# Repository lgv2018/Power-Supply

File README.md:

# Power-Supply
Power supply based on arduino
test on my laptop

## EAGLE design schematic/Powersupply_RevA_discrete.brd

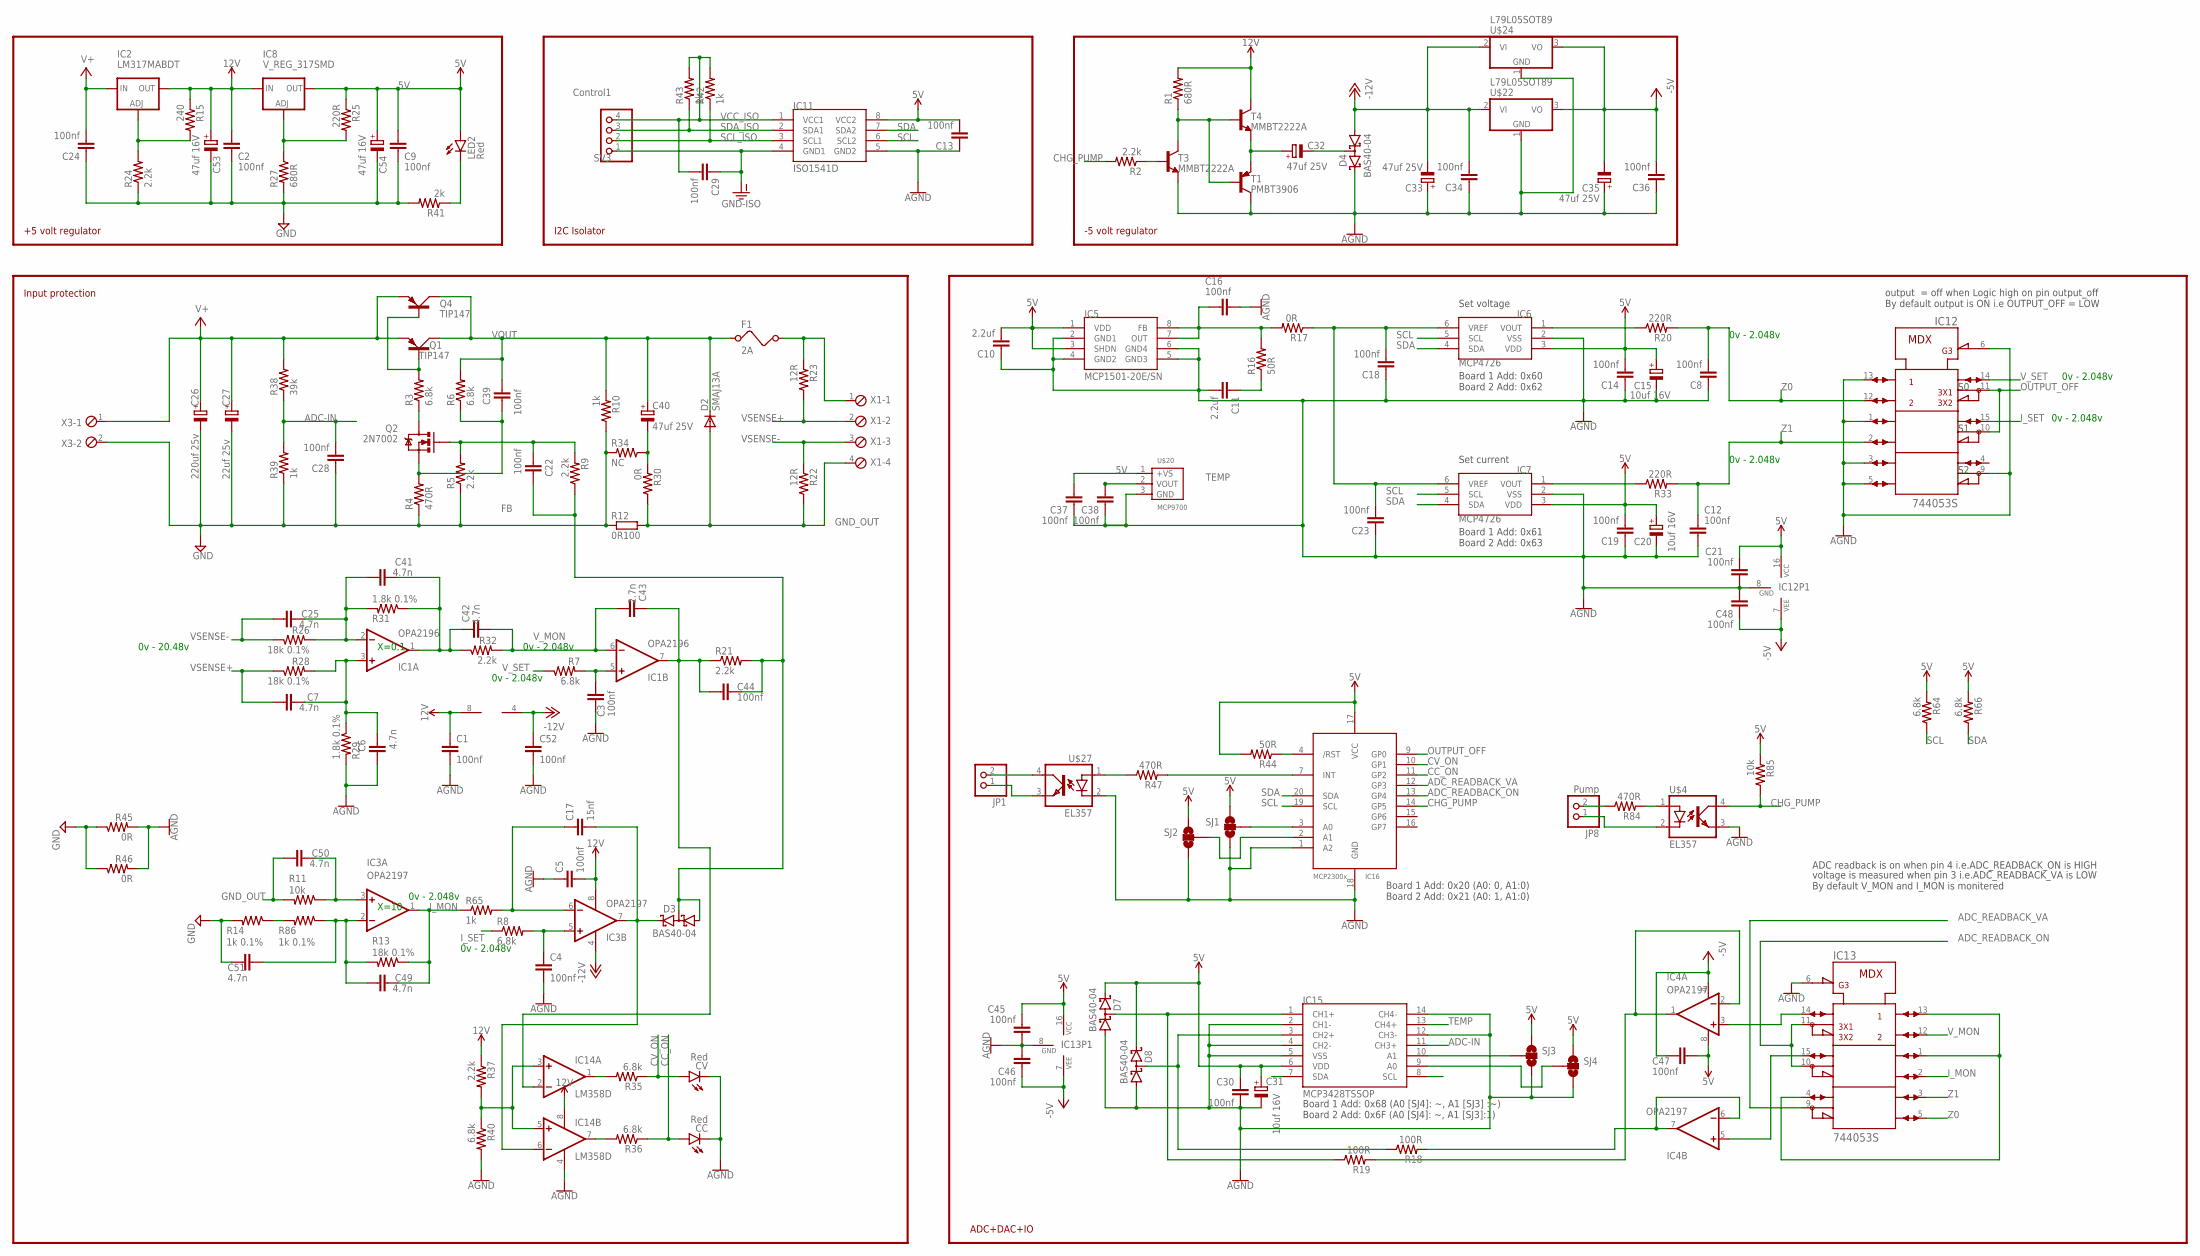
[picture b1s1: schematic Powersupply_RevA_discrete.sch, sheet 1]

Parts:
C1, C2, C3, C5, C8, C9, C12, C13, C14, C16, C18, C19, C21, C23, C24, C28, C29, C30, C34, C36, C37, C38, C39, C44, C45, C46, C47, C48, C52: 100nf; C0603
C4, C22: 100nf; C0805
C6, C7, C25, C41, C42, C49, C50, C51: 4.7n; C0805
C10, C11: 2.2uf; C0805
C15, C20, C31: 10uf 16V; E2-5
C17: 15nf; C0805
C26: 220uf 25v; E3,5-8
C27: 22uf 25v; E3,5-8
C32: 47uf 25V; CT6032
C33, C35, C40: 47uf 25V; E2-5
C43: 2.7n; C0805
C53, C54: 47uf 16V; E2-5
CC: Red; CHIP-LED0805
CV: Red; CHIP-LED0805
D2: SMAJ13A; DO214AC
D3, D4, D7, D8: BAS40-04; SOT23
F1: 2A; FUSE
IC1: OPA2196; SO08
IC2: LM317MABDT; DPACK
IC3, IC4: OPA2197; SO08
IC5: MCP1501-20E/SN; SO-08
IC6, IC7: MCP4726; SOT23-6
IC8: V_REG_317SMD; SOT223
IC11: ISO1541D; SO-08
IC12, IC13: 744053S; SO16
IC14: LM358D; SO08
IC15: MCP3428TSSOP; TSSOP14
IC16: MCP23008QFN20; QFN20
JP1: PINHD-1X2; 1X02
JP8: Pump; 1X02
LED2: Red; CHIP-LED0805
Q1: TIP147; TOP3AV
Q2: 2N7002; SOT23
Q4: TIP147; TO220AV
R1, R27: 680R; R0805
R2, R5, R9, R21, R24, R32, R37: 2.2k; R0805
R3, R6, R7, R8, R35, R36, R40, R64, R66: 6.8k; R0805
R4, R47, R84: 470R; R0805
R10, R39, R42, R43, R65: 1k; R0805
R11, R85: 10k; R0805
R12: 0R100; R2512
R13, R26, R28: 18k 0.1%; R0805
R14, R86: 1k 0.1%; R0805
R15: 240; R0805
R16, R44: 50R; R0805
R17, R30, R45, R46: 0R; R0805
R18, R19: 100R; R0805
R20, R25, R33: 220R; R0805
R22, R23: 12R; R0805
R29, R31: 1.8k 0.1%; R0603
R34: NC; R0805
R38: 39k; R0805
R41: 2k; R0805
SJ1, SJ2, SJ3, SJ4: SOLDERJUMPER_2WAY-OLDS; SJ_3
SV3: Control1; 1X04
T1: PMBT3906; SOT23-BEC
T3, T4: MMBT2222A; SOT23-BEC
U$4, U$27: EL357
U$20: MCP9700; TO92-BCE
U$22, U$24: L79L05SOT89; SOT89
X1: MPT4; 4POL254
X3: MPT2; 2POL254

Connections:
5V: C9.2, C10.2, C13.2, C14.2, C15.+, C19.2, C20.+, C21.2, C30.2, C31.+, C37.2, C45.2, C47.1, C54.+, D7.2 (C2), D8.2 (C2), IC4.8 (V+), IC5.1 (VDD), IC5.3 (SHDN), IC6.3 (VDD), IC7.3 (VDD), IC8.2 (OUT), IC11.8 (VCC2), IC12.16 (VCC), IC13.16 (VCC), IC15.6 (VDD), IC16.17 (VCC), LED2.A, R25.1, R44.2, R64.2, R66.2, R85.2, SJ1.1, SJ2.1, SJ3.1, SJ4.1, U$20.1 (+VS)
12V: C1.1, C2.2, C5.2, C53.+, IC1.8 (V+), IC2.4 (OUT), IC3.8 (V+), IC8.3 (IN), IC14.8 (V+), R1.2, R15.1, R37.1, T4.C
-5V: C35.-, C36.2, C46.1, C47.2, C48.1, IC4.4 (V-), IC12.7 (VEE), IC13.7 (VEE), U$22.3 (VO), U$24.3 (VO)
-12V: C33.-, C34.2, C52.1, D4.1 (A1), IC1.4 (V-), IC3.4 (V-), U$22.2 (VI), U$24.2 (VI)
ADC-IN: C28.2, IC15.11 (CH3+), R38.1, R39.2
ADC-IOUT: IC4.6 (-IN), IC4.7 (OUT), R18.2
ADC-VOUT: IC4.1 (OUT), IC4.2 (-IN), R19.2
ADC_READBACK_ON: IC13.10, IC13.11, IC16.13 (GP4)
ADC_READBACK_VA: IC13.9, IC16.12 (GP3)
AGND: C1.2, C3.2, C4.2, C5.1, C6.2, C8.1, C10.1, C11.2, C12.1, C13.1, C14.1, C15.-, C16.2, C18.1, C19.1, C20.-, C21.1, C23.1, C30.1, C31.-, C33.+, C34.1, C35.+, C36.1, C37.1, C38.1, C45.1, C46.2, C48.2, C52.2, CC.C, CV.C, D4.2 (C2), D7.1 (A1), D8.1 (A1), IC5.2 (GND1), IC5.4 (GND2), IC5.5 (GND3), IC5.6 (GND4), IC6.2 (VSS), IC7.2 (VSS), IC11.5 (GND2), IC12.1, IC12.3, IC12.5, IC12.6 (!G), IC12.8 (GND), IC12.9, IC12.13, IC13.6 (!G), IC13.8 (GND), IC14.4 (V-), IC15.2 (CH1-), IC15.4 (CH2-), IC15.5 (VSS), IC15.12 (CH3-), IC15.14 (CH4-), IC16.1 (A2), IC16.18 (GND), R29.2, R40.2, R45.2, R46.2, SJ1.3, SJ2.3, SJ3.3, SJ4.3, T1.C, T3.E, U$4.3 (EMIT), U$20.3 (GND), U$22.1 (GND), U$24.1 (GND), U$27.2 (C)
CC_ON: CC.A, IC16.11 (GP2), R36.1
CHG_PUMP: IC16.14 (GP5), R2.2, R85.1, U$4.4 (COL)
CV_ON: CV.A, IC16.10 (GP1), R35.1
FB: C22.2, C44.1, D3.1 (A1), D3.3 (C1A2), R9.1, R21.2
GND: C2.1, C9.1, C24.1, C26.-, C27.-, C28.1, C51.1, C53.-, C54.-, R4.1, R5.1, R10.1, R12.1, R14.2, R24.1, R27.2, R34.2, R39.1, R41.2, R45.1, R46.1, X3.2; also elsewhere on the board
GND-ISO: C29.1, IC11.4 (GND1), SV3.1
GND_OUT: C50.2, D2.A, R11.2, R12.2, R22.1, R30.1, X1.4
I_MON: C49.1, IC3.1 (OUT), IC13.2, R13.1, R65.1
I_SET: IC12.15, R8.1
unnamed: C17.1, IC3.6 (-IN), R65.2
unnamed: IC2.1 (ADJ), R15.2, R24.2
unnamed: C50.1, IC3.3 (+IN), R11.1
unnamed: C49.2, C51.2, IC3.2 (-IN), R13.2, R86.1
unnamed: F1.2, R23.2, X1.1
unnamed: R47.1, U$27.1 (A)
unnamed: C25.1, C41.2, IC1.2 (-IN), R26.2, R31.2
unnamed: C16.1, IC5.7 (OUT), IC5.8 (FB), R16.2, R17.2
unnamed: IC14.3 (+IN), IC14.5 (+IN), R37.2, R40.1
unnamed: C43.2, C44.2, IC1.7 (OUT), IC14.2 (-IN), R21.1
unnamed: C6.1, C7.1, IC1.3 (+IN), R28.2, R29.1
unnamed: C17.2, D3.2 (C2), IC3.7 (OUT), IC14.6 (-IN)
unnamed: IC8.1 (ADJ), R25.2, R27.1
unnamed: IC7.1 (VOUT), R33.1
unnamed: C11.1, R16.1
unnamed: C3.1, IC1.5 (+IN), R7.2
unnamed: C4.1, IC3.5 (+IN), R8.2
unnamed: D8.3 (C1A2), IC15.3 (CH2+), R18.1
unnamed: C40.-, R30.2, R34.1
unnamed: IC16.4 (/RST), R44.1
unnamed: IC16.3 (A0), SJ1.2
unnamed: IC4.3 (+IN), IC13.14
unnamed: Q1.B, Q4.B, R3.2
unnamed: LED2.C, R41.1
unnamed: IC4.5 (+IN), IC13.15
unnamed: D7.3 (C1A2), IC15.1 (CH1+), R19.1
unnamed: IC14.1 (OUT), R35.2
unnamed: IC16.2 (A1), SJ2.2
unnamed: IC15.10 (A1), SJ3.2
unnamed: IC15.9 (A0), SJ4.2
unnamed: R2.1, T3.B
unnamed: Q2.3 (D), R3.1
unnamed: R1.1, T1.B, T3.C, T4.B
unnamed: IC13.1, IC13.4, IC13.13
unnamed: C32.+, T1.E, T4.E
unnamed: C32.-, D4.3 (C1A2)
unnamed: IC6.1 (VOUT), R20.1
unnamed: C22.1, Q2.1 (G), R5.2, R9.2
unnamed: IC14.7 (OUT), R36.2
unnamed: C39.1, Q2.2 (S), R4.2, R6.1
unnamed: JP1.2, U$27.4 (COL)
unnamed: C41.1, C42.2, IC1.1 (OUT), R31.1, R32.1
unnamed: JP1.1, U$27.3 (EMIT)
unnamed: IC16.7 (INT), R47.2
unnamed: JP8.2, R84.1
unnamed: R84.2, U$4.1 (A)
unnamed: JP8.1, U$4.2 (C)
unnamed: R14.1, R86.2
OUTPUT_OFF: IC12.10, IC12.11, IC16.9 (GP0)
SCL: IC6.5 (SCL), IC7.5 (SCL), IC11.6 (SCL2), IC15.8 (SCL), IC16.19 (SCL), R64.1
SCL_ISO: IC11.3 (SCL1), R42.1, SV3.2
SDA: IC6.4 (SDA), IC7.4 (SDA), IC11.7 (SDA2), IC15.7 (SDA), IC16.20 (SDA), R66.1
SDA_ISO: IC11.2 (SDA1), R43.1, SV3.3
TEMP: C38.2, IC15.13 (CH4+), U$20.2 (VOUT)
V+: C24.2, C26.+, C27.+, IC2.3 (IN), Q1.E, Q4.E, R38.2, X3.1
VCC_ISO: C29.2, IC11.1 (VCC1), R42.2, R43.2, SV3.4
VOUT: C39.2, C40.+, D2.C, F1.1, Q1.C, Q4.C, R6.2, R10.2
VREF: C18.2, C23.2, IC6.6 (VREF), IC7.6 (VREF), R17.1
VSENSE+: C7.2, R23.1, R28.1, X1.2
VSENSE-: C25.2, R22.2, R26.1, X1.3
V_MON: C42.1, C43.1, IC1.6 (-IN), IC13.12, R32.2
V_SET: IC12.14, R7.1
Z0: C8.2, IC12.12, IC13.5, R20.2
Z1: C12.2, IC12.2, IC13.3, R33.2

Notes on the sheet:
+5 volt regulator
ADC+DAC+IO
Input protection
Board 1 Add: 0x60 Board 2 Add: 0x62
Board 1 Add: 0x61 Board 2 Add: 0x63
Board 1 Add: 0x68 (A0 [SJ4]: ~, A1 [SJ3] :~) Board 2 Add: 0x6F (A0 [SJ4]: ~, A1 [SJ3]:1)
Set voltage
Set current
X=10
X=0.1
0v - 20.48v
0v - 2.048v
-5 volt regulator
I2C Isolator
output = off when Logic high on pin output_off By default output is ON i.e OUTPUT_OFF = LOW
ADC readback is on when pin 4 i.e.ADC_READBACK_ON is HIGH
voltage is measured when pin 3 i.e.ADC_READBACK_VA is LOW By default V_MON and I_MON is monitered
Board 1 Add: 0x20 (A0: 0, A1:0) Board 2 Add: 0x21 (A0: 1, A1:0)

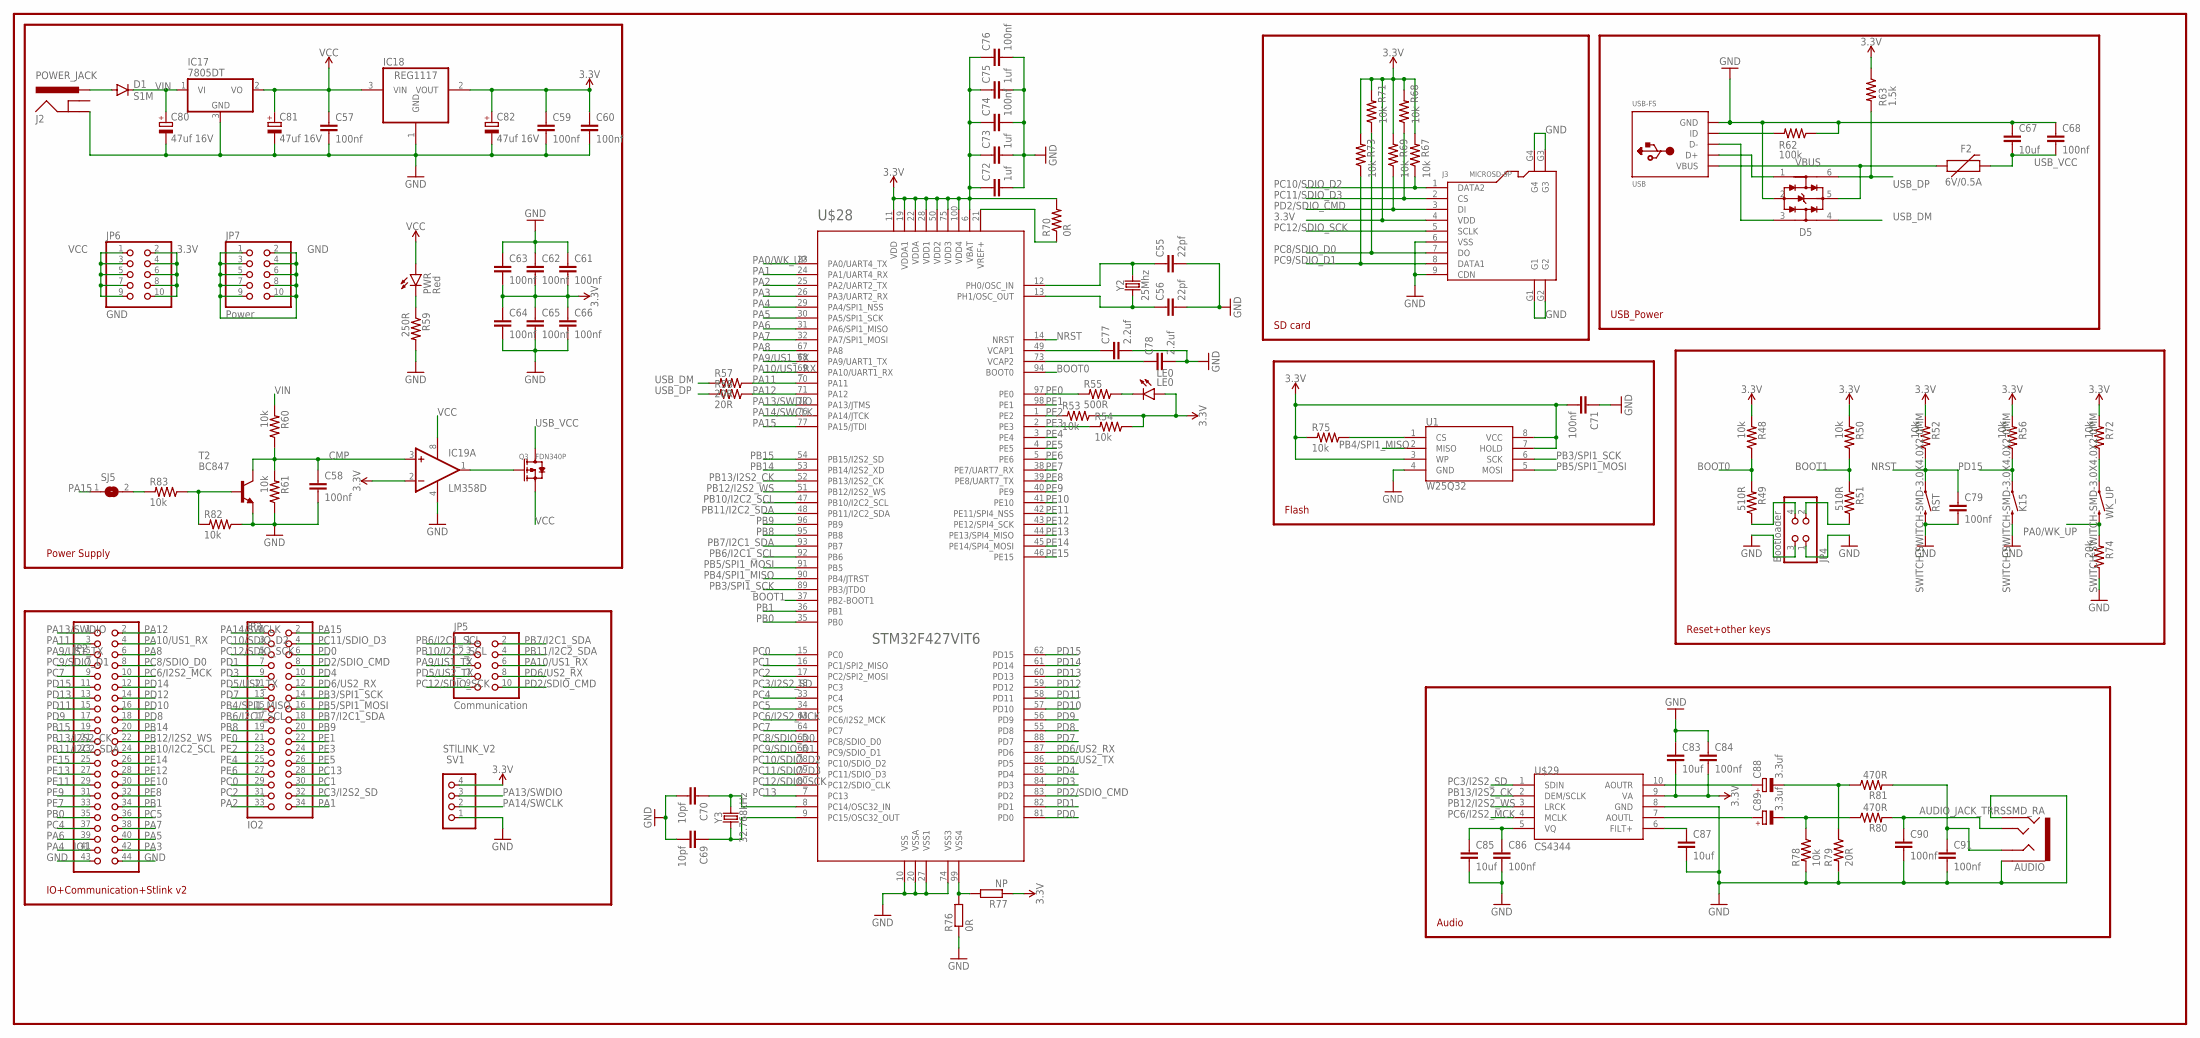
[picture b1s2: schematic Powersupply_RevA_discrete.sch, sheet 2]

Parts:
AUDIO: AUDIO_JACK_TRRSSMD_RA; AUDIO_JACK_3.5MM_TRRS_SMD_RA
C55, C56: 22pf; C0805
C57, C58, C59, C60, C61, C62, C63, C64, C65, C66, C68, C71, C74, C76, C79, C84, C86, C90, C91: 100nf; C0603
C67: 10uf; C0805
C69, C70: 10pf; C0805
C72, C73, C75: 1uf; C0805
C77, C78: 2.2uf; C0805
C80, C81, C82: 47uf 16V; E2-5
C83, C85, C87: 10uf; C1210
C88, C89: 3.3uf; A/3216-18R
D1: S1M; SMA
D5: USBLC6-2P; SOT23-6
F2: 6V/0.5A; 1206
IC17: 7805DT; TO252
IC18: REG1117; SOT223
IC19: LM358D; SO08
J2: POWER_JACK; POWER_JACK_PTH
J3: MICROSD-9P; MICRO-SD9+4P-SMD-16.1X14.5X1.85MM
JP2: IO1; 2X22
JP3: IO2; 2X17
JP4: Bootloader; 2X02
JP5: Communication; 2X05
JP6: GND; 2X05
JP7: Power; 2X05
K15: SWITCH-SWITCH-SMD-3.0X4.0X2.0MM; TACTILE_SWITCH_SMD_6.0X3.5MM
LE0: LE0; CHIP-LED0805
PWR: Red; CHIP-LED0805
Q3: FDN340P; SOT-23
R48, R50, R52, R53, R54, R56, R60, R61, R67, R68, R69, R71, R72, R73, R75, R78, R82, R83: 10k; R0805
R49, R51: 510R; R0805
R55: 500R; R0805
R57, R58, R79: 20R; R0805
R59: 250R; R0805
R62: 100k; R0805
R63: 1.5k; R0805
R70: 0R; R0805
R74: 20k; R0805
R76: 0R; R0402
R77: NP; R0402
R80, R81: 470R; R0805
RST: SWITCH-SWITCH-SMD-3.0X4.0X2.0MM; TACTILE_SWITCH_SMD_6.0X3.5MM
SJ5: SJ
SV1: STlLINK_V2; 1X04
T2: BC847; SOT23
U1: W25Q32; SO08
U$28: STM32F427VIT6; LQFP100
U$29: CS4344; TSSOP10
USB: USB-FS; USB-MINIB
WK_UP: SWITCH-SWITCH-SMD-3.0X4.0X2.0MM; TACTILE_SWITCH_SMD_6.0X3.5MM
Y2: 25Mhz; CRYSTAL-SMD-3.2X2.5MM
Y3: 32.768kHz; CRYSTAL-PTH-2X6-CYL

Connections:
3.3V: C59.1, C60.1, C61.2, C62.2, C63.2, C64.1, C65.1, C66.1, C71.2, C72.1, C73.1, C74.1, C75.1, C76.1, C82.+, C83.2, C84.2, IC18.2 (VOUT), IC19.2 (-IN), J3.4 (VDD), JP6.2, JP6.4, JP6.6, JP6.8, JP6.10, LE0.A, R48.2, R50.2, R52.2, R53.1, R54.1, R56.2, R63.1, R67.2, R68.2, R69.2, R70.2, R71.2, R72.2, R73.2, R75.2, R77.1, SV1.4, U1.3 (WP), U1.7 (HOLD), U1.8 (VCC), U$28.6 (VBAT), U$28.11 (VDD), U$28.19 (VDDA1), U$28.22 (VDDA), U$28.28 (VDD1), U$28.50 (VDD2), U$28.75 (VDD3), U$28.100 (VDD4), U$29.9 (VA)
BOOT0: R48.1, R49.2, U$28.94 (BOOT0)
BOOT1: R50.1, R51.2, U$28.37 (PB2-BOOT1)
CMP: C58.1, IC19.3 (+IN), R60.1, R61.2, T2.3 (C)
GND: AUDIO.EARTH, AUDIO.RING2, C55.2, C56.2, C57.2, C58.2, C59.2, C60.2, C61.1, C62.1, C63.1, C64.2, C65.2, C66.2, C67.1, C68.1, C69.2, C70.2, C71.1, C72.2, C73.2, C74.2, C75.2, C76.2, C77.2, C78.2, C79.2, C80.-, C81.-, C82.-, C83.1, C84.1, C85.2, C86.2, C87.2, C90.2, C91.2, D5.2 (GND), IC17.3 (GND), IC18.1 (GND), IC19.4 (V-), J2.GND, J3.6 (VSS), J3.9 (CDN), J3.G1, J3.G2, J3.G3, J3.G4, JP2.43, JP2.44, JP4.1, JP4.3, JP7.1, JP7.2, JP7.3, JP7.4, JP7.5, JP7.6, JP7.7, JP7.8, JP7.9, JP7.10, K15.2, R59.2, R61.1, R62.1, R74.1, R76.1, R78.2, R79.2, R82.1, RST.2, SV1.1, T2.2 (E), U1.4 (GND), U$28.10 (VSS), U$28.20 (VSSA), U$28.27 (VSS1), U$28.74 (VSS3), U$29.8 (GND), USB.GND; also elsewhere on the board
unnamed: C55.1, U$28.12 (PH0/OSC_IN), Y2.3 (2)
unnamed: C56.1, U$28.13 (PH1/OSC_OUT), Y2.1
unnamed: IC19.1 (OUT), Q3.1 (G)
unnamed: C69.1, U$28.9 (PC15/OSC32_OUT), Y3.1
unnamed: C70.1, U$28.8 (PC14/OSC32_IN), Y3.2
unnamed: R62.2, USB.ID
unnamed: LE0.C, R55.1
unnamed: D1.A, J2.PWR
unnamed: C77.1, U$28.49 (VCAP1)
unnamed: C78.1, U$28.73 (VCAP2)
unnamed: PWR.C, R59.1
unnamed: D5.1 (I/O1-IN), USB.D+
unnamed: JP4.4, R49.1
unnamed: JP4.2, R51.1
unnamed: R82.2, R83.1, T2.1 (B)
unnamed: R83.2, SJ5.2
unnamed: R70.1, U$28.21 (VREF+)
unnamed: R72.1, WK_UP.1
unnamed: R75.1, U1.1 (CS)
unnamed: D5.3 (I/O2-IN), USB.D-
unnamed: R76.2, R77.2, U$28.99 (VSS4)
unnamed: C87.1, U$29.6 (FILT+)
unnamed: C85.1, C86.1, U$29.5 (VQ)
unnamed: C88.+, U$29.10 (AOUTR)
unnamed: C89.+, U$29.7 (AOUTL)
unnamed: C89.-, R78.1, R80.1
unnamed: C88.-, R79.1, R81.1
unnamed: AUDIO.TIP, C90.1, R80.2
unnamed: AUDIO.RING1, C91.1, R81.2
NRST: C79.1, R52.1, RST.1, U$28.14 (NRST)
PA0/WK_UP: R74.2, U$28.23 (PA0/UART4_TX), WK_UP.2
PA1: JP3.34, U$28.24 (PA1/UART4_RX)
PA2: JP3.33, U$28.25 (PA2/UART2_TX)
PA3: JP2.42, U$28.26 (PA3/UART2_RX)
PA4: JP2.41, U$28.29 (PA4/SPI1_NSS)
PA5: JP2.40, U$28.30 (PA5/SPI1_SCK)
PA6: JP2.39, U$28.31 (PA6/SPI1_MISO)
PA7: JP2.38, U$28.32 (PA7/SPI1_MOSI)
PA8: JP2.6, U$28.67 (PA8)
PA9/US1_TX: JP2.5, JP5.5, U$28.68 (PA9/UART1_TX)
PA10/US1_RX: JP2.4, JP5.6, U$28.69 (PA10/UART1_RX)
PA11: JP2.3, R57.1, U$28.70 (PA11)
PA12: JP2.2, R58.1, U$28.71 (PA12)
PA13/SWDIO: JP2.1, SV1.3, U$28.72 (PA13/JTMS)
PA14/SWCLK: JP3.1, SV1.2, U$28.76 (PA14/JTCK)
PA15: JP3.2, SJ5.1, U$28.77 (PA15/JTDI)
PB0: JP2.35, U$28.35 (PB0)
PB1: JP2.34, U$28.36 (PB1)
PB3/SPI1_SCK: JP3.14, U1.6 (SCK), U$28.89 (PB3/JTDO)
PB4/SPI1_MISO: JP3.15, U1.2 (MISO), U$28.90 (PB4/JTRST)
PB5/SPI1_MOSI: JP3.16, U1.5 (MOSI), U$28.91 (PB5)
PB6/I2C1_SCL: JP3.17, JP5.1, U$28.92 (PB6)
PB7/I2C1_SDA: JP3.18, JP5.2, U$28.93 (PB7)
PB8: JP3.19, U$28.95 (PB8)
PB9: JP3.20, U$28.96 (PB9)
PB10/I2C2_SCL: JP2.24, JP5.3, U$28.47 (PB10/I2C2_SCL)
PB11/I2C2_SDA: JP2.23, JP5.4, U$28.48 (PB11/I2C2_SDA)
PB12/I2S2_WS: JP2.22, U$28.51 (PB12/I2S2_WS), U$29.3 (LRCK)
PB13/I2S2_CK: JP2.21, U$28.52 (PB13/I2S2_CK), U$29.2 (DEM/SCLK)
PB14: JP2.20, U$28.53 (PB14/I2S2_XD)
PB15: JP2.19, U$28.54 (PB15/I2S2_SD)
PC0: JP3.29, U$28.15 (PC0)
PC1: JP3.30, U$28.16 (PC1/SPI2_MISO)
PC2: JP3.31, U$28.17 (PC2/SPI2_MOSI)
PC3/I2S2_SD: JP3.32, U$28.18 (PC3), U$29.1 (SDIN)
PC4: JP2.37, U$28.33 (PC4)
PC5: JP2.36, U$28.34 (PC5)
PC6/I2S2_MCK: JP2.10, U$28.63 (PC6/I2S2_MCK), U$29.4 (MCLK)
PC7: JP2.9, U$28.64 (PC7)
PC8/SDIO_D0: J3.7 (DO), JP2.8, R71.1, U$28.65 (PC8/SDIO_D0)
PC9/SDIO_D1: J3.8 (DATA1), JP2.7, R73.1, U$28.66 (PC9/SDIO_D1)
PC10/SDIO_D2: J3.1 (DATA2), JP3.3, R67.1, U$28.78 (PC10/SDIO_D2)
PC11/SDIO_D3: J3.2 (CS), JP3.4, R68.1, U$28.79 (PC11/SDIO_D3)
PC12/SDIO_SCK: J3.5 (SCLK), JP3.5, JP5.9, U$28.80 (PC12/SDIO_CLK)
PC13: JP3.28, U$28.7 (PC13)
PD0: JP3.6, U$28.81 (PD0)
PD1: JP3.7, U$28.82 (PD1)
PD2/SDIO_CMD: J3.3 (DI), JP3.8, JP5.10, R69.1, U$28.83 (PD2)
PD3: JP3.9, U$28.84 (PD3)
PD4: JP3.10, U$28.85 (PD4)
PD5/US2_TX: JP3.11, JP5.7, U$28.86 (PD5)
PD6/US2_RX: JP3.12, JP5.8, U$28.87 (PD6)
PD7: JP3.13, U$28.88 (PD7)
PD8: JP2.18, U$28.55 (PD8)
PD9: JP2.17, U$28.56 (PD9)
PD10: JP2.16, U$28.57 (PD10)
PD11: JP2.15, U$28.58 (PD11)
PD12: JP2.14, U$28.59 (PD12)
PD13: JP2.13, U$28.60 (PD13)
PD14: JP2.12, U$28.61 (PD14)
PD15: JP2.11, K15.1, R56.1, U$28.62 (PD15)
PE0: JP3.21, R55.2, U$28.97 (PE0)
PE1: JP3.22, U$28.98 (PE1)
PE2: JP3.23, R53.2, U$28.1 (PE2)
PE3: JP3.24, R54.2, U$28.2 (PE3)
PE4: JP3.25, U$28.3 (PE4)
PE5: JP3.26, U$28.4 (PE5)
PE6: JP3.27, U$28.5 (PE6)
PE7: JP2.33, U$28.38 (PE7/UART7_RX)
PE8: JP2.32, U$28.39 (PE8/UART7_TX)
PE9: JP2.31, U$28.40 (PE9)
PE10: JP2.30, U$28.41 (PE10)
PE11: JP2.29, U$28.42 (PE11/SPI4_NSS)
PE12: JP2.28, U$28.43 (PE12/SPI4_SCK)
PE13: JP2.27, U$28.44 (PE13/SPI4_MISO)
PE14: JP2.26, U$28.45 (PE14/SPI4_MOSI)
PE15: JP2.25, U$28.46 (PE15)
USB_DM: D5.4 (I/O2-OUT), R57.2
USB_DP: D5.6 (I/O1-OUT), R58.2, R63.2
USB_VCC: C67.2, C68.2, F2.2, Q3.3 (D)
VBUS: D5.5 (VBUS), F2.1, USB.VBUS
VCC: C57.1, C81.+, IC17.2 (VO), IC18.3 (VIN), IC19.8 (V+), JP6.1, JP6.3, JP6.5, JP6.7, JP6.9, PWR.A, Q3.2 (S)
VIN: C80.+, D1.C, IC17.1 (VI), R60.2

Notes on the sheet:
Power Supply
IO+Communication+Stlink v2
SD card
Flash
USB_Power
Reset+other keys
Audio

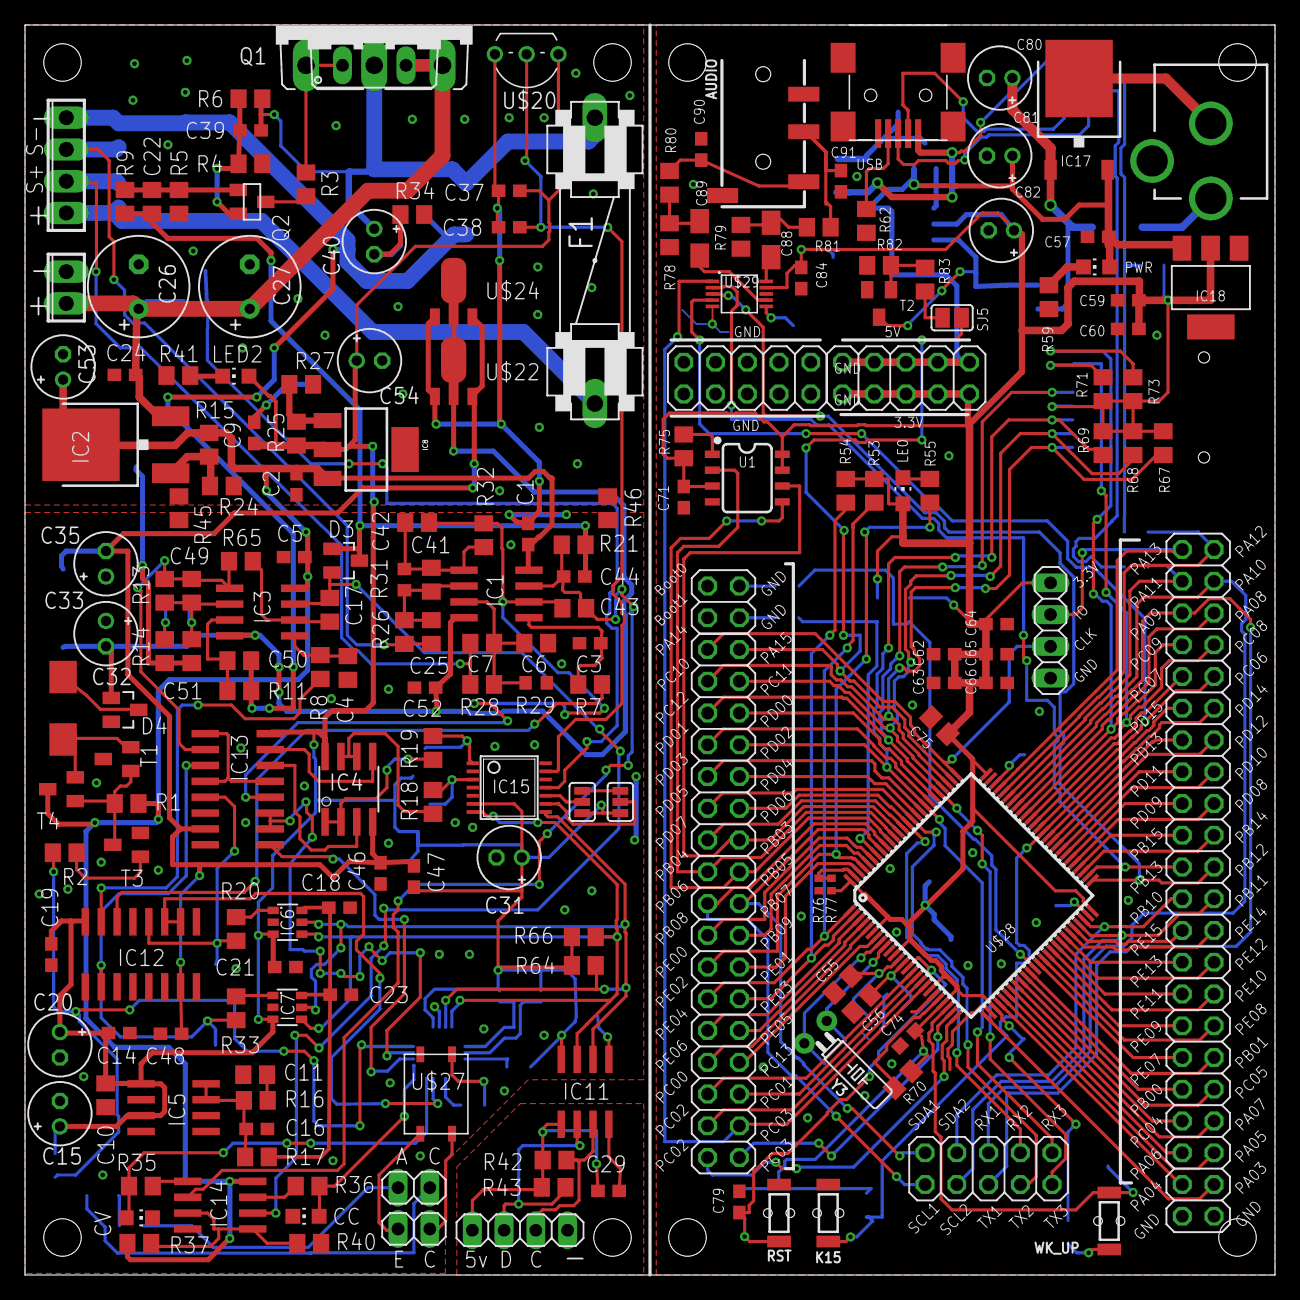
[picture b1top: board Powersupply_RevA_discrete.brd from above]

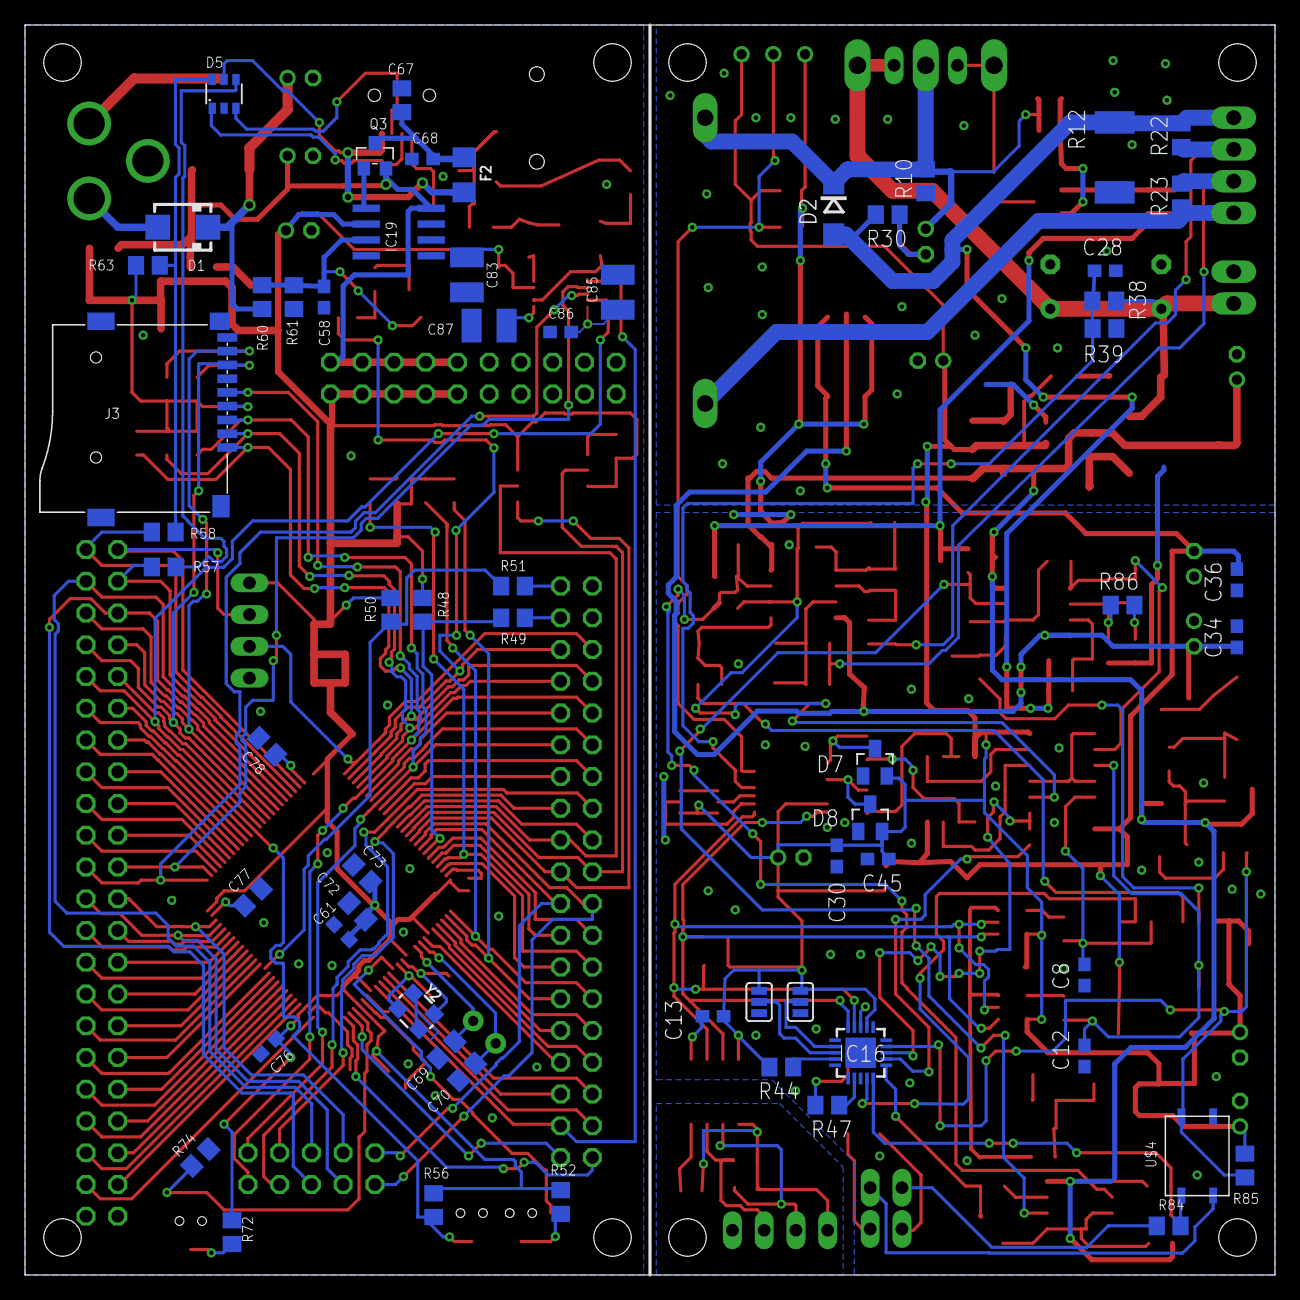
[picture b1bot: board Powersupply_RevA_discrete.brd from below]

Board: 2 copper layers, 100.0 x 100.0 mm, 250 parts (62 on the bottom side), 200 nets.

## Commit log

2019-05-24 commit from mylaptop
2019-05-24 added index file
2019-05-24 changed index file
2019-05-24 Commited to test branch
2019-05-24 commited power supply project
2019-05-24 file deleted
2019-05-24 file added
2019-05-25 update1
2019-05-25 Auto return feature added
2019-05-25 Keypad feature added
2019-05-25 Keypad feature complete
2019-05-26 optimization
2019-05-26 Added calibration
2019-05-26 improvement
2019-05-26 change of buttons
2019-05-27 Two point calibration added
2019-05-29 Calibration saving to EEPROM feature added
2019-05-30 optimization of code
2019-05-30 littlebit cleaning
2019-06-01 little bit cleanup+ powercard as class
2019-06-02 Powercard class added + code optimization
2019-07-19 test
2019-07-19 test1
2019-08-23 calibration menu improvement
2019-09-01 added watt feature
2019-09-01 code cleanup
2019-09-19 added other documents
2019-09-26 commit1

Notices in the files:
parts and their libraries:
SparkFun-Retired: Licensing: Creative Commons ShareAlike 4.0 International - https://creativecommons.org/licenses/by-sa/4.0
